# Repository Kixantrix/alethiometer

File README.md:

# The Alethiometer

A working alethiometer — the symbolic truth-reading instrument from Philip Pullman's
*His Dark Materials* — as a website.

**Live site:** https://kixantrix.github.io/alethiometer/

**The physical instrument:** a hand-held brass alethiometer with three thumbwheel-set hands,
a motor-driven needle and a hidden speaker and microphone. It's built from laser-cut brass
(SendCutSend) and an ESP32-S3, and uses the same oracle as the site.
See [`hardware/`](hardware/README.md) for the design, the parts to order and assembly, and
[`firmware/`](firmware/README.md) for the code.

## How to use it

1. **Ask a question** — type it, or tap the microphone and speak it (Chrome/Edge).
2. **Frame it with three hands** — click a hand chip (I, II, III) to select it, then click a
   symbol on the dial. The three symbols you choose set the context and register of your
   question, just as in the books. Hover any symbol to see its layered meanings.
3. **Press Ask** — the blue needle sweeps the dial, stopping at a sequence of symbols.
   The number of swings at each stop tells you which level of that symbol's meaning applies.
   The interpretation appears below the device.

## How it works

- **Frontend** — vanilla HTML/CSS/JS, no build step, hosted on GitHub Pages. The dial is an
  SVG with the 36 classic symbols; needle animation is requestAnimationFrame with easing.
- **The scholar** — readings are composed by `gpt-5-mini` on Azure OpenAI (Responses API),
  reached through a small Azure Function (`api/`) so the API key never leaves the server.
  For questions about current events ("is the USA still in the World Cup?"), the model uses
  its built-in `web_search` tool to learn the truth before composing the reading, and the
  consulted sources appear beneath the interpretation. The function validates input,
  rate-limits, and returns strict JSON:
  `{"reading": [{"symbol", "swings"}...], "interpretation", "sources"}`.
- **Fallback oracle** — if the API can't be reached, the device composes a deterministic
  local reading from your question and chosen symbols, so it always answers.
- **Speech** — browser Web Speech API; no audio ever leaves your machine except to your
  browser's own speech service.

## Symbol meanings

The 36 symbols follow book canon and the reading tradition of alethiometrist fan
scholarship (each symbol carries an infinite descent of meanings; three are listed per
symbol in `js/symbols.js`).

## Development

Serve locally (the API allows `http://localhost:8000` via CORS):

```sh
python -m http.server 8000
```

### Azure resources (resource group `rg-alethiometer`, eastus2)

| Resource | Purpose |
|---|---|
| `aoai-alethiometer-kx` | Azure OpenAI, `gpt-5-mini` (+ speech model) deployments |
| `func-alethiometer-kx` | Azure Function (Node 24, consumption) — `ask`, `ask-voice`, `speak` endpoints |
| `stalethiometerkx` | Storage for the Function App |

Deploy the API after changes:

```powershell
Compress-Archive -Path api\* -DestinationPath api.zip -Force
az functionapp deployment source config-zip --name func-alethiometer-kx `
  --resource-group rg-alethiometer --src api.zip --build-remote true
```

The function needs app settings `AOAI_ENDPOINT`, `AOAI_API_KEY`, `AOAI_DEPLOYMENT`
(set in Azure, never committed).

### Physical instrument API

The brass alethiometer (ESP32-S3 with mic + speaker) uses two extra endpoints in
`api/src/functions/voice.js`. Both require header `x-device-key` matching app setting
`DEVICE_KEY` (503 if unset, 401 if wrong) and are rate-limited to 10 requests/minute.

- **`POST /api/ask-voice?symbols=Hourglass%7CSun%7CMoon`** — body is raw WAV
  (`Content-Type: audio/wav`, 16 kHz mono 16-bit PCM, ≤ 15 s / 1,000,000 bytes, else 413).
  The question is transcribed, then read exactly like `/api/ask`. Returns
  `{"question", "reading": [{"symbol", "swings"}...], "interpretation", "sources"}`;
  422 `{"error", "code": "no_speech"}` if nothing intelligible was heard.
- **`POST /api/speak`** — JSON `{"text": "..."}` (1-2000 chars). Streams back raw PCM
  speech in an oracular voice: `Content-Type: audio/pcm`,
  `x-audio-format: pcm_s16le;rate=24000;channels=1`.

Extra app settings: `DEVICE_KEY` (required), `AOAI_TRANSCRIBE_DEPLOYMENT`
(default `gpt-4o-mini-transcribe`), `AOAI_TTS_DEPLOYMENT` (default `gpt-4o-mini-tts`),
`AOAI_TTS_VOICE` (default `sage`). Streaming responses need `@azure/functions` ≥ 4.3 and
Functions host ≥ 4.28 (enabled via `app.setup({ enableHttpStream: true })`).

Create the speech model deployments in the existing Azure OpenAI resource (check available
versions first; `2025-12-15` was current at time of writing, `2025-03-20` is the original):

```powershell
az cognitiveservices account list-models --name aoai-alethiometer-kx `
  --resource-group rg-alethiometer `
  --query "[?contains(name, 'mini-transcribe') || contains(name, 'mini-tts')].{name:name, version:version}" -o table

az cognitiveservices account deployment create --name aoai-alethiometer-kx `
  --resource-group rg-alethiometer --deployment-name gpt-4o-mini-transcribe `
  --model-name gpt-4o-mini-transcribe --model-version <version> --model-format OpenAI `
  --sku-name GlobalStandard --sku-capacity 1

az cognitiveservices account deployment create --name aoai-alethiometer-kx `
  --resource-group rg-alethiometer --deployment-name gpt-4o-mini-tts `
  --model-name gpt-4o-mini-tts --model-version <version> --model-format OpenAI `
  --sku-name GlobalStandard --sku-capacity 1

az functionapp config appsettings set --name func-alethiometer-kx `
  --resource-group rg-alethiometer --settings `
  DEVICE_KEY=<long-random-secret> `
  AOAI_TRANSCRIBE_DEPLOYMENT=gpt-4o-mini-transcribe `
  AOAI_TTS_DEPLOYMENT=gpt-4o-mini-tts `
  AOAI_TTS_VOICE=sage
```

## Ideas for v2

- Ornate hand-drawn symbol artwork replacing the emoji glyphs
- Spoken readings (text-to-speech in an oracular voice)
- A "study mode" that teaches the symbol meanings

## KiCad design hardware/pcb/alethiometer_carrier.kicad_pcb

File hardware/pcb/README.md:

# Carrier PCB

One octagonal, two-layer, **all through-hole** board in the bottom of the case. It replaces the
point-to-point wiring. **Every module plugs into sockets**, so you can pull any of them to
reflash, probe or replace it without desoldering anything. The crown switch and the wall USB-C
port are mounted on the board too, so their push and plug forces go into the screwed-down
carrier rather than a glue joint. So are the power slide switch and the battery's
JST-PH socket. The two off-board parts (mic, speaker) plug into PicoBlade headers J4 and J5. Every signal also has a labelled test pad. The underside carries a line drawing of the finished instrument in the silkscreen, drawn from the CAD by [`emblem_art.py`](emblem_art.py) (re-run it after a CAD change, then `make_pcb.py`).

| File | What it is |
|---|---|
| `make_pcb.py` | Generates the whole board from [`../cad/layout.py`](../cad/layout.py) (the same positions the CAD model uses) |
| `alethiometer_carrier.kicad_pcb` | The KiCad 10 board. Open it to inspect or tweak. |
| `fab/alethiometer_carrier_gerbers.zip` | **Upload this to the PCB fab** |
| `fab/plot_top.pdf`, `fab/plot_bottom.pdf` | 1:1 prints for checking parts against the board before soldering |
| `fab/render_top.png`, `fab/render_bottom.png` | 3D renders |
| `NETLIST.md` | Every net and the pads on it |
| `drc_report.json` | KiCad DRC (0 violations, 0 unconnected) |
| `alethiometer.pretty/` | Footprints: the Adafruit modules, the X27, and Unexpected Maker's ProS3 (CERN-OHL-1.2) |

## Ordering the board

JLCPCB, PCBWay, OSH Park and similar fabs all work. Upload `fab/alethiometer_carrier_gerbers.zip`
and pick:

- **2 layers, FR-4, 1.6 mm**, 1 oz copper;
- HASL (lead-free) or ENIG, any solder-mask colour;
- assembly: see [Factory assembly](#factory-assembly) (recommended), or none to build it yourself;
- leave "remove order number" at the default, or pay for it.

The board is about 108 mm across, a little over the 100 × 100 mm price break, so expect roughly $10–20 for five
boards plus shipping.

## Factory assembly

Recommended: have the fab solder every through-hole part on the board, so the only soldering left
to you is the modules' own header pins, J7's USB cable and the mic and speaker pigtails. That
takes about 130 joints off your bench.

**Order it from PCBWay as turnkey through-hole (THT) assembly.** Upload, together:

- `fab/alethiometer_carrier_gerbers.zip` (the board);
- `fab/assembly_bom.csv`: every part the fab fits, with manufacturer part numbers (the parts
  marked **fab** in the table below);
- `fab/assembly_cpl.csv`: where each one goes (designator, X, Y, side, rotation).

Both CSVs are generated from the board by [`assembly_files.py`](assembly_files.py) (also run by
`make_pcb.py`). Notes for the quote:

- **The sockets must be Adafruit #3008 (5 mm body, DigiKey 1528-3008-ND)**, cut to the lengths in the
  BOM's notes, and fitted square and flat. Don't accept a substitute: the height stack under P1 is
  built on exactly 5 mm, and the common single-row sockets (LCSC's included) are 8.5 mm, which would
  push the AS5600s into their magnets. If PCBWay can't source #3008, send them one pack as
  consigned parts, or have them fit everything else and solder the sockets yourself (step 4 below).
- JLCPCB is not recommended here: it only fits parts from its LCSC library (no 5 mm socket), and
  consigned parts need a JLC part number or engineering approval.
- Budget about $15–30 for the assembly of one or two boards.
- What you get checked: the bare boards are **100 % electrically tested** against the netlist (opens
  and shorts), and the assembled board gets **optical inspection** (AOI). Neither powers it up, so
  still do the [bring-up checklist](#bring-up-checklist), and check that each module plugs in
  level when the boards arrive.

## Bill of materials (carrier)

| Ref | Part | Qty | Notes |
|---|---|---|---|
| — | Carrier PCB (above) | 1 | |
| U1 | **Unexpected Maker ProS3[D]** (ESP32-S3, Adafruit #6398; the original ProS3 also fits) | 1 | Solder its two 1×17 male headers on, pins down |
| U2–U4 | **Adafruit AS5600** magnetic angle sensor, STEMMA QT (#6357) | 3 | Header included. Use the 1×6 row only. **Magnets not included**; see the main BOM. |
| U5 | **Adafruit DRV8833** dual H-bridge (#3297) | 1 | Header included (1×8 + 1×6) |
| U6 | **Adafruit MAX98357A** I2S amp (#3006) | 1 | Header included. Boards since mid-2024 come with a screw terminal soldered in the speaker holes: remove it (snip the plastic, pull each pin out while heating it, clear the holes with wick) |
| M1 | **Juken/Switec X27.168** gauge stepper (keep its internal stop) | 1 | Adafruit #2424 or AliExpress |
| — | **Short female header, 0.1", 5 mm body** (Adafruit #3008, 5 × 36-pin; DigiKey 1528-3008-ND) | 1 pack | Cut into every socket: 2× 1×17 (ProS3), 3× 1×6 + 3× 1×2 (AS5600 + rest posts), 1×8 + 1×6 (DRV8833), 1×7 + 2× 1×1 (MAX98357A), 2× 1×4 (X27). About 110 of the 180 positions. **fab**|
| — | Male header strip 0.1", 1×40 | 1 | MAX98357A speaker pins, J1 (and J2 if wanted) |
| U7 | **Adafruit USB Type C breakout, downstream (#4090)** | 1 | Wall USB-C port. Header included; 5.1 kΩ CC resistors on board. Plugs into a 1×8 socket. |
| — | M2 nylon round spacer, 5 mm × Ø4.5; M2 × 10 screw; M2 nut | 2 each | Clamp U7 down beside its receptacle (screw from the top, nut under the carrier) |
| SW1 | **Omron (Aratas) B3F-3152** right-angle 6 × 6 mm tactile switch (or the B3F-3150 when in stock; not the B3F-3100, whose plunger is 3 mm shorter) | 1 | Crown switch, soldered at the top-right corner **fab**|
| — | Short USB-C cable **with data** (USB 2.0), thin (≤ 3.5 mm) | 1 | Cut to ~6 cm from the plug: ProS3 USB-C → J7. Check D+/D− continuity first; charge-only cables won't work. |
| R1, R3, R5 | 10 kΩ, ¼ W metal film, 0.4" (10.16 mm) lead pitch | 3 | Series resistors of the hand-sensor dividers **fab**|
| R2, R4, R6 | 47 kΩ, ¼ W metal film | 3 | Divider shunts (`HAND_DIVIDER_RATIO` = 57/47 in firmware) **fab**|
| SW2 | **C&K OS102011MA1QN1** right-angle SPDT slide switch | 1 | Power, on the back edge; reached through a slot in the back wall **fab**|
| J8 | **JST S2B-PH-K-S** side-entry 2-pin socket, 2.0 mm | 1 | Battery plug. Polarity is marked on the silkscreen. **fab**|
| C1 | 100 µF 10–16 V aluminium electrolytic, radial Ø6.3 mm, 2.5 mm pitch, **≤ 11 mm tall** (a 6.3 × 7 can is ideal) | 1 | Bulk cap on VBAT for the motor and amp. **Polarised.** **fab**|
| J4, J5 | **Molex PicoBlade** 1.25 mm vertical headers **53047-0510** (5-pin) and **53047-0210** (2-pin) | 1 each | Mic and speaker plug in here **fab**|
| — | PicoBlade-compatible pre-crimped pigtails, 5-way and 2-way, ~10 cm | 1 each | Soldered at the INMP441 and the speaker |
| — | M2 nylon round spacer, 2.5 mm × Ø4.5 | 3 | Between the case floor and the board |
| — | M2 × 12 mm brass hex standoff, female-female | 3 | Board → P1 |
| — | M2 × 8 mm brass slotted countersunk screw, DIN 963, 90° | 3 | Flush case floor → spacer → board → standoff; length includes head |
| — | Kapton tape | | One layer on the case floor under the board |

## How it goes together

The board stands on three nylon spacers above a Kapton-lined floor. Brass M2 × 12 standoffs carry
plate P1 above it. The top-right corner has no bay post, which leaves room for the crown switch;
P1's corner there sits on a short M2 × 4 F-F standoff instead (it doesn't reach the board). Around the post holes the board has a 3.4 mm
copper keep-out, so the brass case never touches a net. Every module rests **directly on its 5 mm sockets**: its male header is
soldered with the black plastic spacer on top, which is then pulled off (step 4 below). The bay
height is set by the AS5600 chain (socket 5 + board and chip 3.1 + 1.1 mm air gap + Ø6×2.5 magnet
+ 0.3 mm below P1 = 12 mm). The sockets cost about 4 mm of case height compared with soldering the
modules flat.

```
 P1 (brass)                 ────────────────────────────────────────
                                magnet ▒▒        X27 body ██████
 M2×12 standoff ║          AS5600 ▬▬▬▬▬▬▬           │  │
                ║          socket ▮   rest post ▮   socket
 carrier PCB    ═══════════════════════════════════════════════════
 nylon spacer   ▯  Kapton  ─────────────────────────────────────────
 case floor     ════════════════════════════════════════════════════
```

**Socket positions** (the silkscreen shows the module outlines and every pin name):

- **ProS3 (U1).** Two 1×17 rows, with its USB-C toward the left. The ProS3 has no USB data pins
  on its headers, so a short cut-down USB-C cable runs from its port to **J7** (VBUS red,
  D− white, D+ green, GND black). The board carries those four lines to the wall port U7. Put a
  dot of hot glue on the cable jacket near J7 as strain relief.
- **Wall USB-C (U7).** The Adafruit #4090 breakout plugs into a 1×8 socket with its receptacle
  facing the right wall. Two M2 × 10 screws go through its mounting holes (right beside the
  receptacle) and 5 mm nylon spacers, with nuts under the carrier, so plugging in pushes on
  screws, not on the socket. Its mouth sits about 1.5 mm inside the outer face, behind a
  10 × 4.4 mm opening that hugs the port (plugs with short shells may not latch fully).
- **Crown switch (SW1).** An Omron B3F-3152 (or B3F-3150) right-angle tactile switch soldered at the top-right
  corner, its button on the crown axis. The turned brass crown's stem presses it through the lower
  case's chamfer.
- **AS5600 ×3 (U2–U4).** Each chip sits exactly under its sensor shaft. The 1×6 row faces the
  dial centre. A **rest post** under the far edge (just a bare 1×2 socket) holds the board level at the
  same height as the header row. Its
  pads are grounded. Only VIN, GND and OUT are used; leave SDA, SCL and 3Vo unconnected.
- **DRV8833 (U5).** A 1×8 row (VM … AIN1) and a 1×6 row (AO1 … BSEN). BSEN and ASEN are grounded on the board.
- **MAX98357A (U6).** The 1×7 row, plus two single-pin sockets under its **SPK−/SPK+** holes. Solder a
  single male pin into each of those holes. They carry the speaker signal to **J5** and support
  the board's far edge.
- **X27.168 (M1).** Its four rear pins plug into two 1×4 sockets cut from the same 5 mm strip
  (outer positions only). Solder them square with the other sockets: the board's hole positions set
  the motor mesh, like every other gear centre (`cad/mesh.py`).

**Off-board connections.** The mic and speaker plug into **J4** and **J5**, vertical PicoBlade
headers: header and mated plug stand about 6.5 mm, well under P1 (12 mm). Solder pre-crimped
pigtails to the INMP441 and the speaker; they plug in before the movement frame goes down
(ASSEMBLY.md §6.3) and unplug when it is lifted out. J1 and J2 take ordinary vertical male headers
(8.5 mm fits under P1); you only plug into J1 on the bench, with the movement lifted off.

| Ref | Pins (silkscreen) | Goes to |
|---|---|---|
| J1 DEBUG | GND 3V3 TX RX IO0 RST 5V BAT | USB-serial adapter / probes. Hold IO0 low and tap RST for ROM download mode. |
| J2 SPARE GPIO | GND 3 38 34 35 36 37 | Free ESP32-S3 pins for later ideas (IO39–42 stay free on the ProS3, unrouted) |
| J4 MIC | VDD GND SCK WS SD | INMP441 (tie its L/R pin to GND at the mic) |
| J5 SPKR | + − | 28 mm speaker |
| J7 USB CABLE | VBUS D− D+ GND | Cut USB-C cable from the ProS3's own port (wire colours on the silkscreen) |

## Assembly order

If the board came factory-assembled, only steps 4 (the modules' header pins, using the fitted
sockets as the jig) and 7 (screwing down U7 and the J7 cable) are left.

1. **Check the bare board** with a multimeter. The GND test pad must not be shorted to `VBAT`,
   `+5V`, `+3V3` or `3V3_SW`.
2. **Resistors and C1.** R1–R6 lie flat. C1's long leg (+) goes to the square pad marked `+`.
   Clip the leads.
3. **Male header** for J1 (and J2 if you want it).
4. **Module sockets: use the modules as jigs.** Cut each socket strip to length (you lose one
   position at each cut; file it smooth) and drop the strips into the board, unsoldered.
   Push the module's male header **long pins down** through the module's holes and into the
   sockets, so the black plastic spacer sits on *top* of the module and the module sits flat on
   the sockets (and on the bare rest-post socket for the AS5600s). Solder **one** socket pin from
   underneath, check that everything is square and flat, then solder the rest. Solder the header
   pins on top of the module. Then slide the plastic spacer up and off with pliers, and clip the
   stubs flush. The MAX98357A's two speaker pins are single header pins fitted the same way.
   Every module now unplugs and drops back in at exactly the right height.
5. **Power switch and J8.** Solder SW2 and J8 flat on the board. The battery itself goes in later,
   just before the bench test ([ASSEMBLY.md §4.3](../ASSEMBLY.md#43-battery)); before plugging it
   in, check with a meter that its red wire meets J8's **+** pin, and if not, swap the two crimps in
   its plug (lift the tabs with a pin).
6. **X27 sockets, J4 and J5.** Solder the X27's two 1×4 sockets (plug the motor in as a jig so they
   stand square, then take it out again: it goes in through P1 in ASSEMBLY.md §6) and the two
   PicoBlade headers.
7. **SW1 and U7.** Solder the crown switch flat on the board. Screw U7 down: M2 × 10 screws from
   the top through U7, the 5 mm spacers and the board, with nuts underneath. Cut a USB-C cable
   about 6 cm from the plug, strip the four wires and solder them into J7 by colour. Plug it into
   the ProS3.
8. **Kapton** on the case floor. Spacers, board, then the standoffs, fixed with M2 × 8
   countersunk screws from below. Machine the flush seats in the brass case beforehand
   ([ASSEMBLY.md §1](../ASSEMBLY.md#1-prepare-the-laser-cut-parts)); do not countersink the PCB
   or nylon spacers.

## Bring-up checklist

Do this on the bench before closing the case. Everything is reachable from the top through
the **test pads** in the bottom strip and J1. Every pad is labelled with its net.

| Step | Fitted | Check |
|---|---|---|
| 1 | Bare board + passives | Resistance GND↔`+3V3`, `+5V`, `VBAT`, `3V3_SW` all > 1 kΩ. `H1`/`H2`/`H3` → GND ≈ 47 kΩ. |
| 2 | ProS3 only, USB connected | `+5V` ≈ 5.0 V, `+3V3` ≈ 3.3 V, `VBAT` ≈ 4.2 V (charging or battery). Flash the firmware (see [`../../firmware/README.md`](../../firmware/README.md)) and open the serial monitor. |
| 3 | + AS5600 ×3 | `3V3_SW` ≈ 3.3 V while awake. `hands` prints three angles. Turning a magnet over each chip moves `H1`–`H3` between about 0 and 2.7 V. |
| 4 | + DRV8833 + X27 | `FLT` reads high (no fault). `home` buzzes the needle against its stop, and `sweep` visits the symbols. You can scope `AIN1`/`AIN2`/`BIN1`/`BIN2`. If it homes the wrong way, set `MOTOR_PHASE_DIR = -1`. |
| 5 | + MAX98357A + speaker | `tone` (or `tone 440`) beeps. `AMP_SD` is high while it plays. `BCLK`/`WS`/`DOUT` carry I2S. |
| 6 | + INMP441 on J4 | `rec` records and plays back. `MIC_SD` carries data. |
| 7 | Crown / power | Press the crown: `status` shows it, and a crown press wakes it from `sleep`. Power switch off: `BAT+` and `VBAT` disconnect (on battery, it goes dark). |

**Firmware iteration.** The ProS3's native USB (CDC serial + the ESP32-S3's built-in USB-JTAG
auto-reset) reaches the wall port through J7 and U7, so `pio run -t upload` works with
the case closed. Over the air (OTA) works once a device key is set. If a bad build ever
bricks USB, use J1 with any 3.3 V USB-serial adapter: TX↔RX, RX↔TX, GND; hold IO0 to GND and
tap RST.

## Regenerating

You need KiCad 10 and Java 17+. Download `freerouting-1.9.0.jar` from
[github.com/freerouting/freerouting/releases](https://github.com/freerouting/freerouting/releases).
Freerouting 2.x's native CLI crashes on Windows.

```powershell
& "$env:LOCALAPPDATA\Programs\KiCad\10.0\bin\python.exe" hardware\pcb\make_pcb.py --freerouting path\to\freerouting-1.9.0.jar
```

The script places everything from `cad/layout.py`, routes the board (power nets 0.6 mm,
signals 0.35 mm, GND pours on both sides), refills the zones, runs DRC and exports `fab/`. If you
move a module in `layout.py`, rerun this script and `cad/build.py` together. The CAD model uses
the same positions.

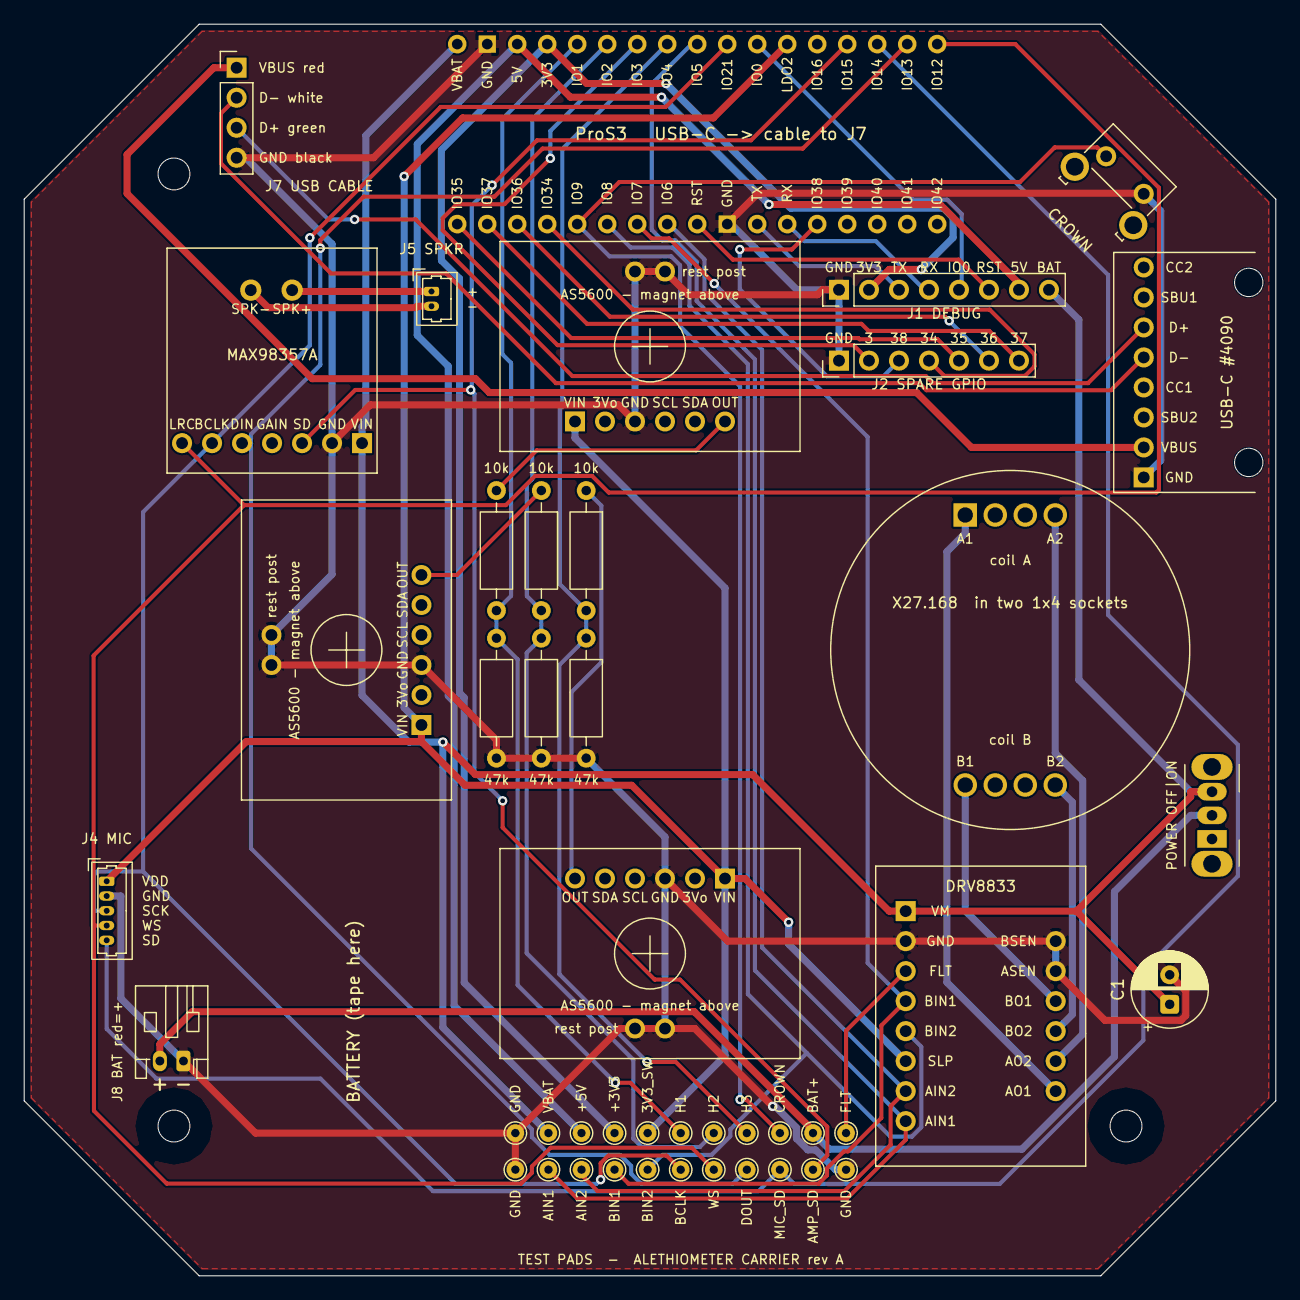
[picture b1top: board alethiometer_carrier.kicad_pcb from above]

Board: 2 copper layers, 106.0 x 106.0 mm, 48 parts (0 on the bottom side), 42 nets.

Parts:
C1: 100uF 10V; CP_Radial_D6.3mm_P2.50mm
H1, H2, H3: M2 post; MountingHole_2.7mm_M2.5
J1: DEBUG; PinHeader_1x08_P2.54mm_Vertical
J2: SPARE GPIO; PinHeader_1x07_P2.54mm_Vertical
J4: MIC; Molex_PicoBlade_53047-0510_1x05_P1.25mm_Vertical
J5: SPKR; Molex_PicoBlade_53047-0210_1x02_P1.25mm_Vertical
J7: USB CABLE; PinHeader_1x04_P2.54mm_Vertical
J8: LiPo JST-PH; JST_PH_S2B-PH-K_1x02_P2.00mm_Horizontal
M1: X27.168; X27_168_socketed
R1, R3, R5: 10k; R_Axial_DIN0207_L6.3mm_D2.5mm_P10.16mm_Horizontal
R2, R4, R6: 47k; R_Axial_DIN0207_L6.3mm_D2.5mm_P10.16mm_Horizontal
SW1: B3F-3150 crown; SW_SPST_Omron_B3F-315x_Angled
SW2: POWER; SW_Slide_SPDT_Angled_CK_OS102011MA1Q
TP1, TP12, TP22: GND; TestPoint_THTPad_D1.5mm_Drill0.7mm
TP2: VBAT; TestPoint_THTPad_D1.5mm_Drill0.7mm
TP3: +5V; TestPoint_THTPad_D1.5mm_Drill0.7mm
TP4: +3V3; TestPoint_THTPad_D1.5mm_Drill0.7mm
TP5: 3V3_SW; TestPoint_THTPad_D1.5mm_Drill0.7mm
TP6: H1; TestPoint_THTPad_D1.5mm_Drill0.7mm
TP7: H2; TestPoint_THTPad_D1.5mm_Drill0.7mm
TP8: H3; TestPoint_THTPad_D1.5mm_Drill0.7mm
TP9: CROWN; TestPoint_THTPad_D1.5mm_Drill0.7mm
TP10: BAT+; TestPoint_THTPad_D1.5mm_Drill0.7mm
TP11: FLT; TestPoint_THTPad_D1.5mm_Drill0.7mm
TP13: AIN1; TestPoint_THTPad_D1.5mm_Drill0.7mm
TP14: AIN2; TestPoint_THTPad_D1.5mm_Drill0.7mm
TP15: BIN1; TestPoint_THTPad_D1.5mm_Drill0.7mm
TP16: BIN2; TestPoint_THTPad_D1.5mm_Drill0.7mm
TP17: BCLK; TestPoint_THTPad_D1.5mm_Drill0.7mm
TP18: WS; TestPoint_THTPad_D1.5mm_Drill0.7mm
TP19: DOUT; TestPoint_THTPad_D1.5mm_Drill0.7mm
TP20: MIC_SD; TestPoint_THTPad_D1.5mm_Drill0.7mm
TP21: AMP_SD; TestPoint_THTPad_D1.5mm_Drill0.7mm
U1: UM ProS3; ProS3_TH
U2: AS5600 hand I; Adafruit_AS5600_6357
U3: AS5600 hand II; Adafruit_AS5600_6357
U4: AS5600 hand III; Adafruit_AS5600_6357
U5: DRV8833; Adafruit_DRV8833_3297
U6: MAX98357A; Adafruit_MAX98357A_3006
U7: USB-C wall port; Adafruit_USB_C_4090

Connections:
3V3_SW: J4.1, TP5.1, U1.12, U2.1, U3.1, U4.1, U5.6
+3V3: J1.2, TP4.1, U1.4
+5V: J1.7, TP3.1, U1.3
AIN1: TP13.1, U1.9, U5.8
AIN2: TP14.1, U1.27, U5.7
AMP_SD: TP21.1, U1.14, U6.3
AOUT1: M1.1, U5.9
AOUT2: M1.2, U5.10
BAT+: J8.2, SW2.2, TP10.1
BCLK: J4.3, TP17.1, U1.10, U6.6
BIN1: TP15.1, U1.28, U5.4
BIN2: TP16.1, U1.29, U5.5
BOUT1: M1.3, U5.12
BOUT2: M1.4, U5.11
CROWN: SW1.1, TP9.1, U1.30
DOUT: TP19.1, U1.16, U6.5
FLT: TP11.1, U5.3
GND: C1.2, J1.1, J2.1, J4.2, J7.4, J8.1, R2.2, R4.2, R6.2, SW1.2, TP1.1, TP12.1, TP22.1, U1.2, U1.25, U2.3, U2.7, U2.8, U3.3, U3.7, U3.8, U4.3, U4.7, U4.8, U5.2, U5.13, U5.14, U6.2, U7.1
H1: R1.2, R2.1, TP6.1, U1.5
H1_OUT: R1.1, U2.6
H2: R3.2, R4.1, TP7.1, U1.6
H2_OUT: R3.1, U3.6
H3: R5.2, R6.1, TP8.1, U1.8
H3_OUT: R5.1, U4.6
IO0: J1.5, U1.11
IO3: J2.2, U1.7
IO34: J2.4, U1.31
IO35: J2.5, U1.34
IO36: J2.6, U1.32
IO37: J2.7, U1.33
IO38: J2.3, U1.22
MIC_SD: J4.5, TP20.1, U1.15
RST: J1.6, U1.26
RX: J1.4, U1.23
SPK+: J5.1, U6.9
SPK-: J5.2, U6.8
TX: J1.3, U1.24
USB_D+: J7.3, U7.6
USB_D-: J7.2, U7.5
USB_VBUS: J7.1, U7.2
VBAT: C1.1, J1.8, SW2.3, TP2.1, U1.1, U5.1, U6.1
WS: J4.4, TP18.1, U1.17, U6.7
